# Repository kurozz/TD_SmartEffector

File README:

# Tree Diagram Smart Effector design files repository.

Based on the Duet3D Smart Effector, see www.duet3d.com for the original Duet3D Smart Effector information. This reproduction/modification is not endorsed or supported in any way by Duet3D

This design is meant for 24V, 12V is possible but requires dessoldering LEDs and adding jumpers.

## Changes from the original Smart Effector v3.0:
- Connectors heavily modified
    - All cables from the Duet controller board on a single connector
    - All cables from the effector on the same side of the board
- 6 illumination LEDs instead of 3.
- LEDs are 24V only. You can use 12V by soldering jumpers in place of 3 LEDs.
- Different regulator and amplifier to be easier to source.
- Works with the same firmware as Smart Effector v3.0.

Tree Diagram Smart Effector

Design by Kuro.

Original Design by Tony Lock and David Crocker

LICENSE: see the LICENSE file in the repository

Documentation: https://docs.duet3d.com/Duet3D_hardware/Accessories/Smart_Effector

Developed in KiCAD v6: https://www.kicad.org/

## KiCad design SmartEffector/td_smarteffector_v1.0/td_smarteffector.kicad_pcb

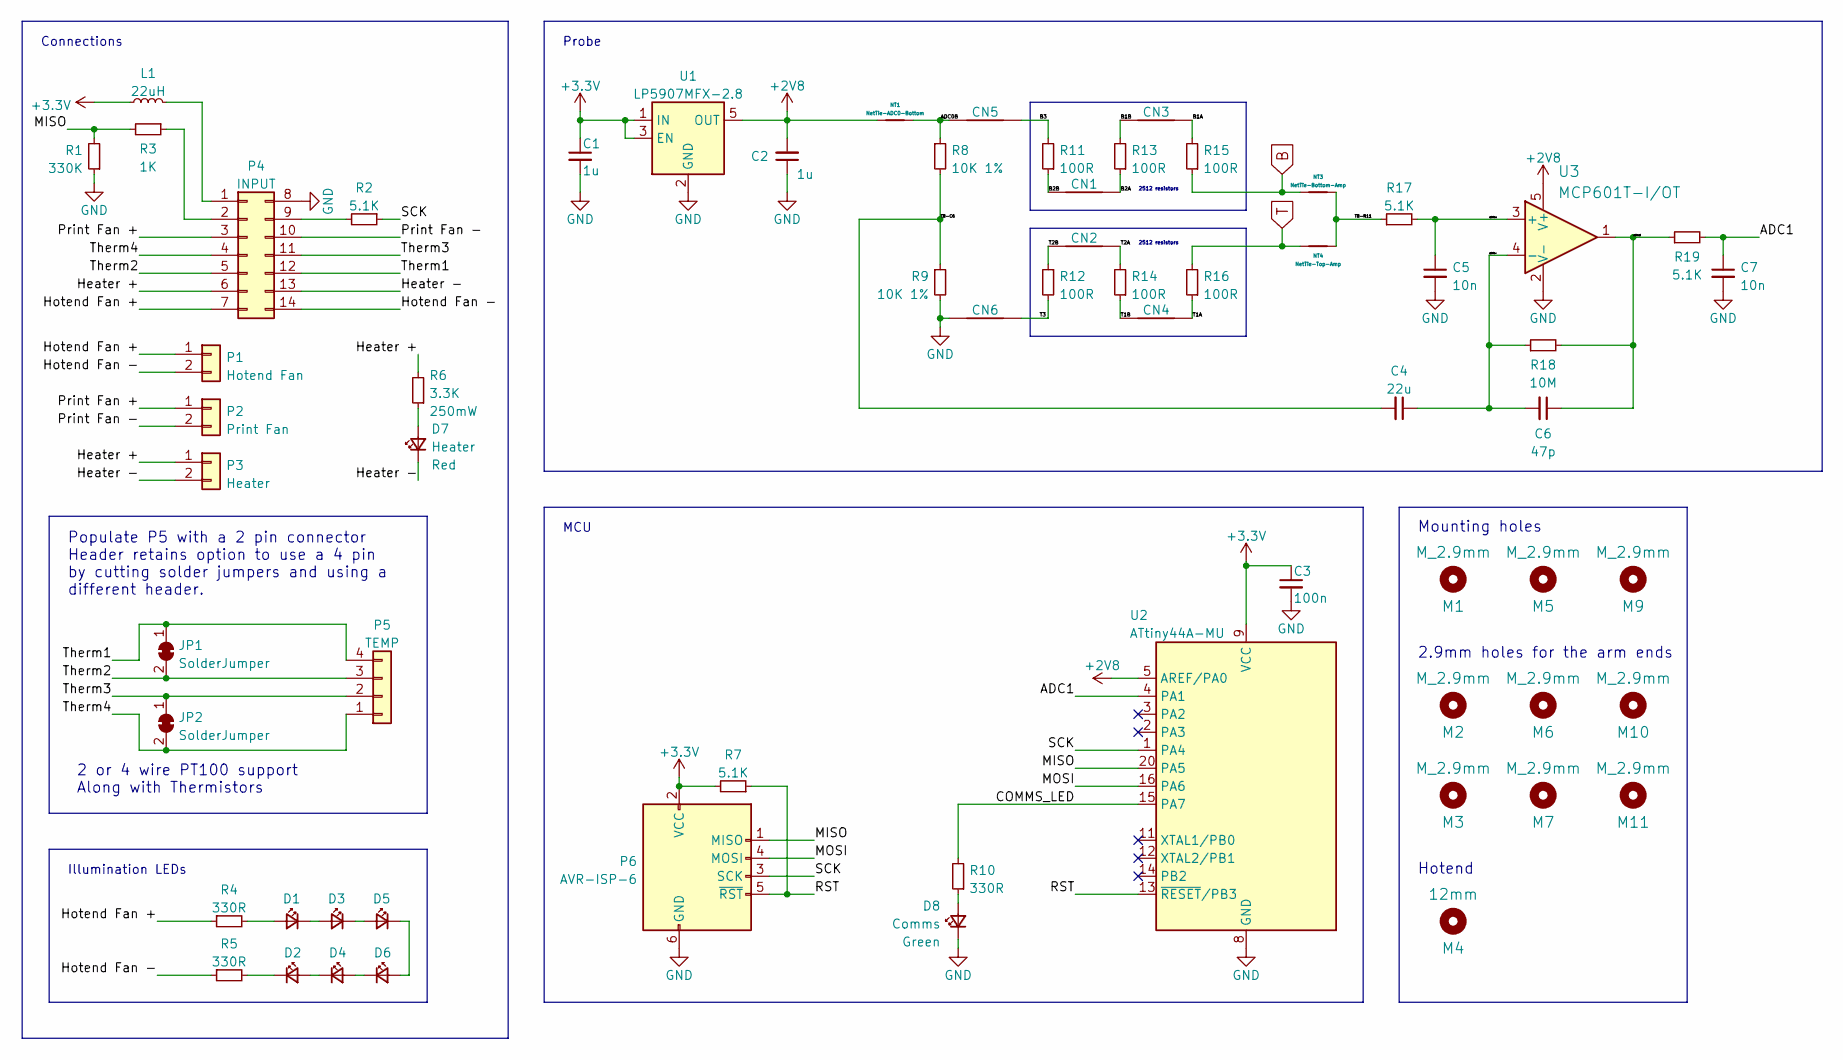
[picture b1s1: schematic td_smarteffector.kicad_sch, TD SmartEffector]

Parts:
C1, C2: 1u; C_0603_1608Metric; LCSC C15849
C3: 100n; C_0402_1005Metric; LCSC C307331
C4: 22u; C_0805_2012Metric; LCSC C602037
C5, C7: 10n; C_0402_1005Metric; LCSC C15195
C6: 47p; C_0603_1608Metric; LCSC C1671
CN1, CN3: Round_Track_Connector; round_track_connection_bot_01
CN2, CN4: Round_Track_Connector; round_track_connection_top_01
CN5: Round_Track_Connector; round_track_connection_bot_02
CN6: Round_Track_Connector; round_track_connection_top_02
D1, D2, D3, D4, D5, D6: illum; LED_PLCC_2835_Handsoldering
D7: Heater; LED_0603_1608Metric_Pad1.05x0.95mm_HandSolder
D8: Comms; LED_0603_1608Metric_Pad1.05x0.95mm_HandSolder
JP1, JP2: SolderJumper; SolderJumper-2_P1.3mm_Bridged_RoundedPad1.0x1.5mm
L1: 22uH; L_0805_2012Metric; LCSC C223175
M1, M2, M3, M5, M6, M7, M9, M10, M11: M_2.9mm; MountingHole_3mm
M4: 12mm; 12mmHole
NT1: NetTie-ADC0-Bottom; NetTie-2_SMD_Pad0.5mm
NT3: NetTie-Bottom-Amp; NetTie-2_SMD_Pad0.5mm
NT4: NetTie-Top-Amp; NetTie-2_SMD_Pad0.5mm
P1: Hotend Fan; Molex_KK-254_AE-6410-02A_1x02_P2.54mm_Vertical
P2: Print Fan; Molex_KK-254_AE-6410-02A_1x02_P2.54mm_Vertical
P3: Heater; Molex_Micro-Fit_3.0_43650-0215_1x02_P3.00mm_Vertical
P4: INPUT; Molex_Micro-Fit_3.0_43045-1412_2x07_P3.00mm_Vertical
P5: TEMP; Molex_KK-254_AE-6410-04A_1x04_P2.54mm_Vertical
P6: AVR-ISP-6; PinHeader_2x03_P2.54mm_Vertical_SMD
R1: 330K; R_0402_1005Metric; LCSC C25778
R2, R7, R17, R19: 5.1K; R_0402_1005Metric; LCSC C25905
R3: 1K; R_0402_1005Metric; LCSC C11702
R4, R5: 330R; R_0805_2012Metric; LCSC C17630
R6: 3.3K; R_0805_2012Metric; LCSC C2759303
R8, R9: 10K 1%; R_0402_1005Metric; LCSC C25744
R10: 330R; R_0402_1005Metric; LCSC C25104
R11, R12, R13, R14, R15, R16: 100R; R_2512_6332Metric; LCSC C309610
R18: 10M; R_0603_1608Metric; LCSC C7250
U1: LP5907MFX-2.8; SOT-23-5; Part Number LP5907MFX-2.8/NOPB; LCSC C186700
U2: ATtiny44A-MU; QFN-20-1EP_4x4mm_P0.5mm_EP2.6x2.6mm; Part Number ATtiny44A-MUR; LCSC C123718
U3: MCP601T-I/OT; SOT-23-5; Part Number MCP601T-I/OT; LCSC C128440

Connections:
+2V8: C2.2, NT1.1, U1.5 (OUT), U2.5 (AREF/PA0), U3.5 (V+)
+3V3: C1.1, C3.1, L1.1, P6.2 (VCC), R7.2, U1.1 (IN), U1.3 (EN), U2.9 (VCC)
/ADC0B: CN5.1, NT1.2, R8.1
/ADC1: C7.1, R19.2, U2.4 (PA1)
/B1A: CN3.1, R15.2
/B1B: CN3.2, R13.2
/B2A: CN1.1, R13.1
/B2B: CN1.2, R11.1
/B3: CN5.2, R11.2
/COMMS_LED: R10.2, U2.15 (PA7)
/Heater +: P3.1, P4.6, R6.2
/Heater -: D7.1 (K), P3.2, P4.13
/Hotend Fan +: P1.1, P4.7, R4.1
/Hotend Fan -: P1.2, P4.14, R5.1
/MISO: P6.1 (MISO), R1.2, R3.2, U2.20 (PA5)
/MOSI: P6.4 (MOSI), U2.16 (PA6)
/Print Fan +: P2.1, P4.3
/Print Fan -: P2.2, P4.10
/RST: P6.5 (~RST), R7.1, U2.13 (~RESET/PB3)
/SCK: P6.3 (SCK), R2.1, U2.1 (PA4)
/T1A: CN4.1, R16.1
/T1B: CN4.2, R14.1
/T2A: CN2.1, R14.2
/T2B: CN2.2, R12.1
/T3: CN6.2, R12.2
/TB-C6: C4.2, R8.2, R9.1
/TB-R11: NT3.2, NT4.2, R17.1
/Therm1: JP1.1 (A), P4.12, P5.4
/Therm2: JP1.2 (B), P4.5, P5.3
/Therm3: JP2.1 (A), P4.11, P5.2
/Therm4: JP2.2 (B), P4.4, P5.1
/u3Vout: C6.1, R18.2, R19.1, U3.1
/u3vin+: C5.1, R17.2, U3.3 (+)
/u3vin-: C4.1, C6.2, R18.1, U3.4 (-)
B: NT3.1, R15.1
GND: C1.2, C2.1, C3.2, C5.2, C7.2, CN6.1, D8.1 (K), P4.8, P6.6 (GND), R1.1, R9.2, U1.2 (GND), U2.8 (GND), U2.21 (GND), U3.2 (V-)
unnamed: D1.1 (K), D3.2 (A)
unnamed: D1.2 (A), R4.2
unnamed: D2.1 (K), R5.2
unnamed: D2.2 (A), D4.1 (K)
unnamed: D3.1 (K), D5.2 (A)
unnamed: D4.2 (A), D6.1 (K)
unnamed: D5.1 (K), D6.2 (A)
unnamed: D7.2 (A), R6.1
unnamed: D8.2 (A), R10.1
unnamed: L1.2, P4.1
unnamed: P4.2, R3.1
unnamed: P4.9, R2.2
T: NT4.1, R16.2

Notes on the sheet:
2.9mm holes for the arm ends
2512 resistors
Mounting holes
Hotend
Probe
MCU
Populate P5 with a 2 pin connector Header retains option to use a 4 pin by cutting solder jumpers and using a different header.
Illumination LEDs
Connections
2 or 4 wire PT100 support Along with Thermistors

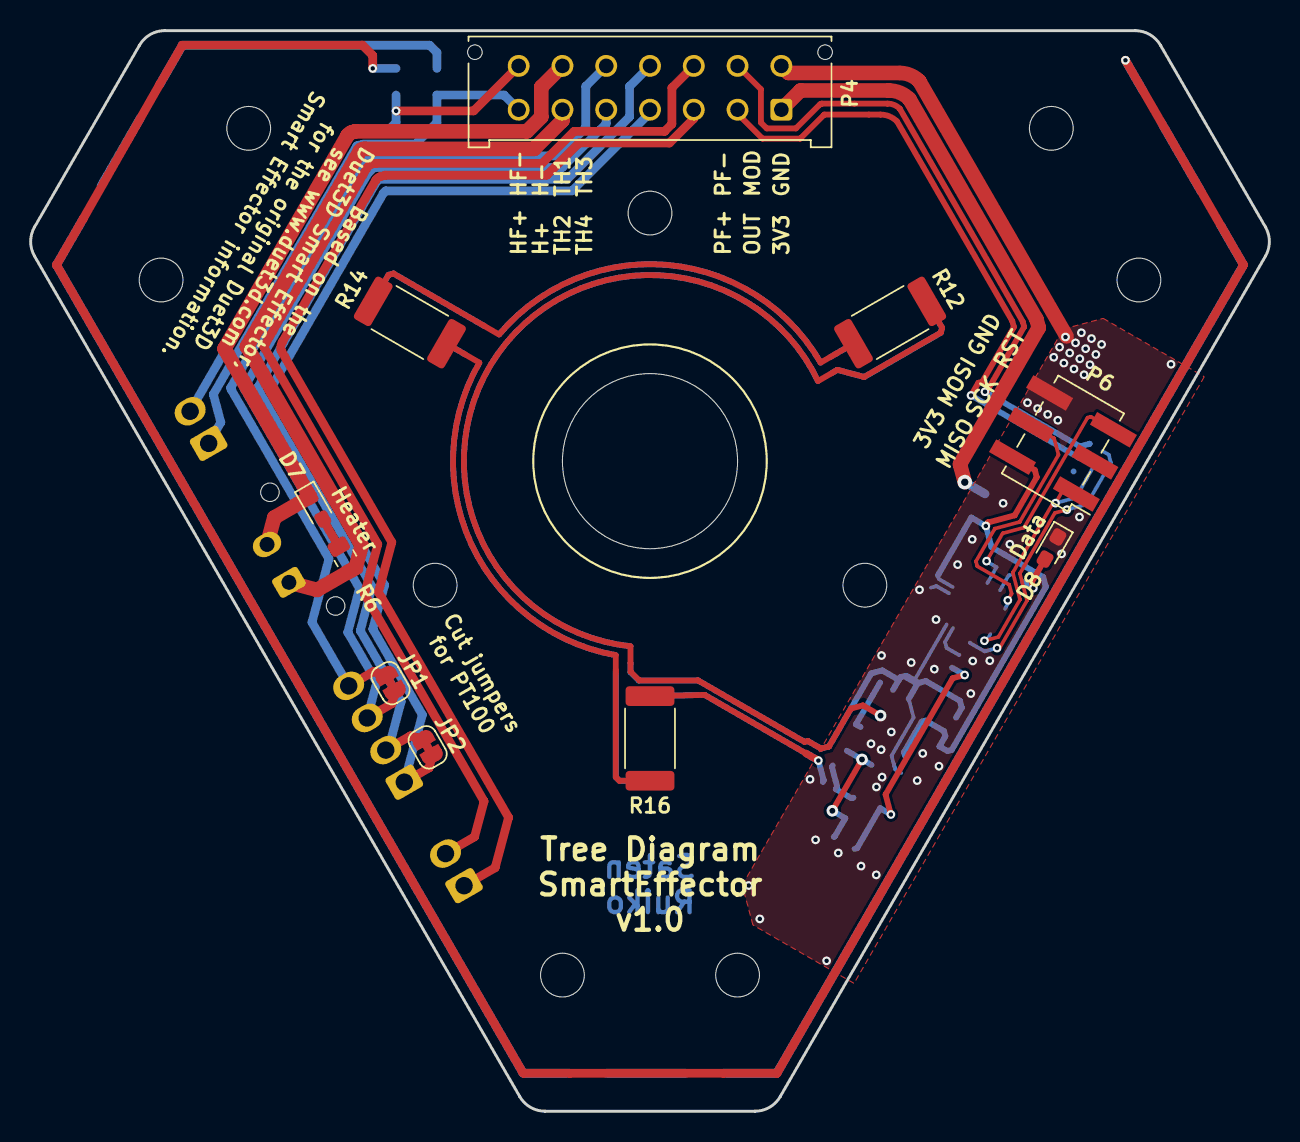
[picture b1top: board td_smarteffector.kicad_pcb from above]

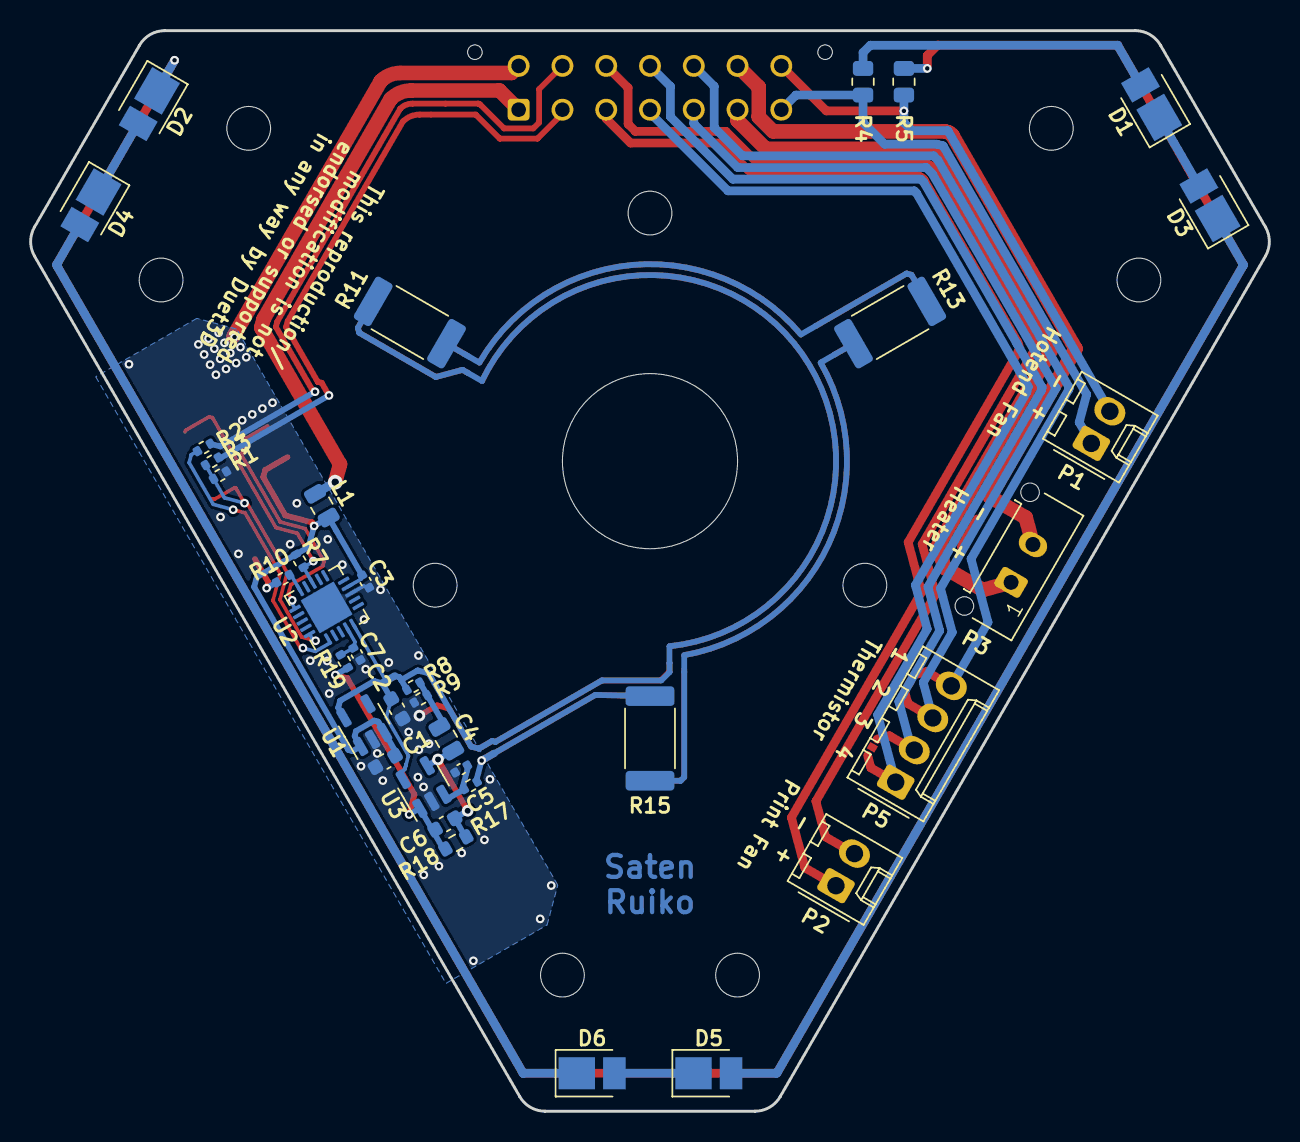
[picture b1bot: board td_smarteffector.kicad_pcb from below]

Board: 2 copper layers, 84.9 x 74.0 mm, 65 parts (38 on the bottom side), 49 nets.

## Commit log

2022-11-18 Initial commit for TD Smart Effector.
2022-11-18 Updated README.
2022-11-18 Rename README to README.md
